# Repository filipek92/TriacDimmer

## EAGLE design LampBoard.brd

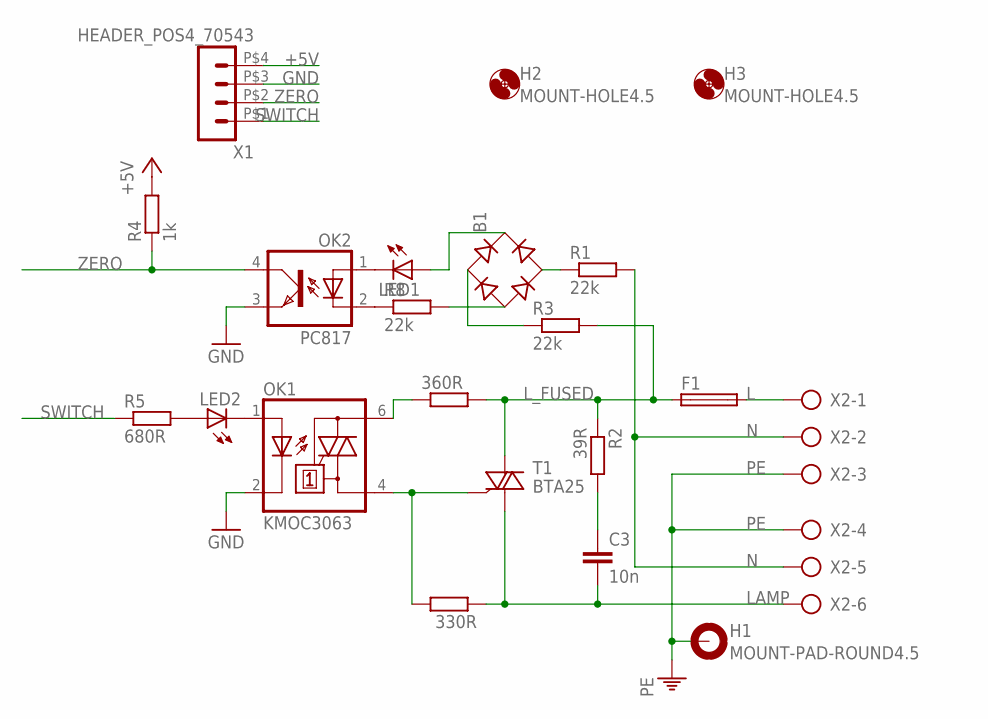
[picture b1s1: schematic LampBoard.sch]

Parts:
330R, 360R: R-EU_0411/12; 0411/12
B1: B-DIL
C3: 10n; C050-045X075
F1: SH22,5A
H1: MOUNT-PAD-ROUND4.5; 4,5-PAD
H2, H3: MOUNT-HOLE4.5; 4,5
LED1, LED2: LED3MM
OK1: KMOC3063; DIL06
OK2: PC817; DIL04
R1, R3, R8: 22k; 0207/10
R2: 39R; 0411/12
R4: 1k; M0805
R5: 680R; M0805
T1: BTA25; TO220BV
X1: HEADER_POS4_70543; 70543-POS4
X2: AK300/6

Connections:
22K: B1.AC2, R1.1
+5V: R4.2, X1.P$4 (4)
GND: OK1.2 (C), OK2.3 (EMIT), X1.P$3 (3)
L: F1.2, X2.1
LAMP: 330R.1, C3.2, T1.T1 (A1), X2.6
L_FUSED: 360R.2, F1.1, R2.1, R3.2, T1.T2 (A2)
N: R1.2, X2.2, X2.5
unnamed: C3.1, R2.2
unnamed: 360R.1, OK1.6 (A2)
unnamed: 330R.2, OK1.4 (A1), T1.G
unnamed: LED1.K (C), OK2.1 (A)
unnamed: B1.AC1, R3.1
unnamed: LED2.K (C), OK1.1 (A)
unnamed: OK2.2 (C), R8.1
unnamed: B1.+, LED1.A
unnamed: LED2.A, R5.2
unnamed: B1.-, R8.2
PE: H1.B4,5, X2.3, X2.4
SWITCH: R5.1, X1.P$1 (1)
ZERO: OK2.4 (COL), R4.1, X1.P$2 (2)

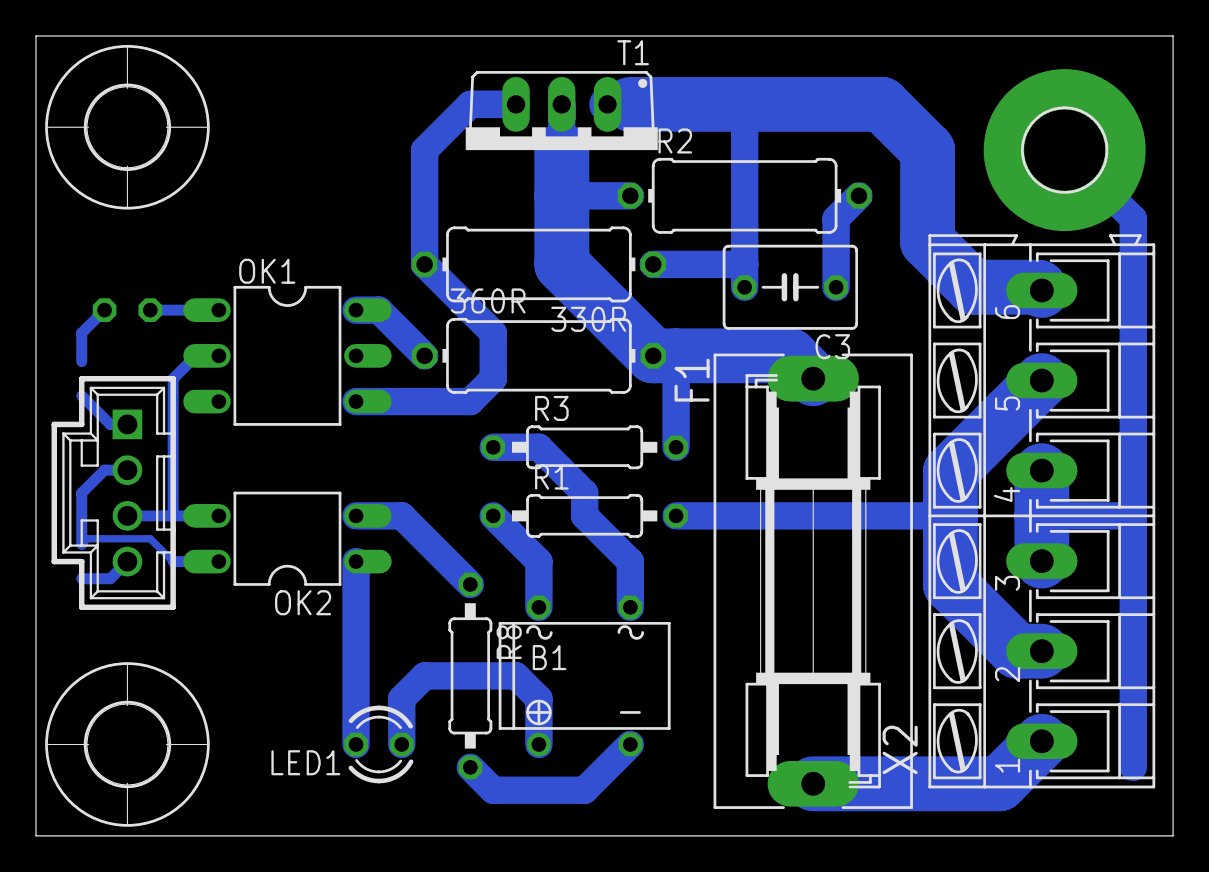
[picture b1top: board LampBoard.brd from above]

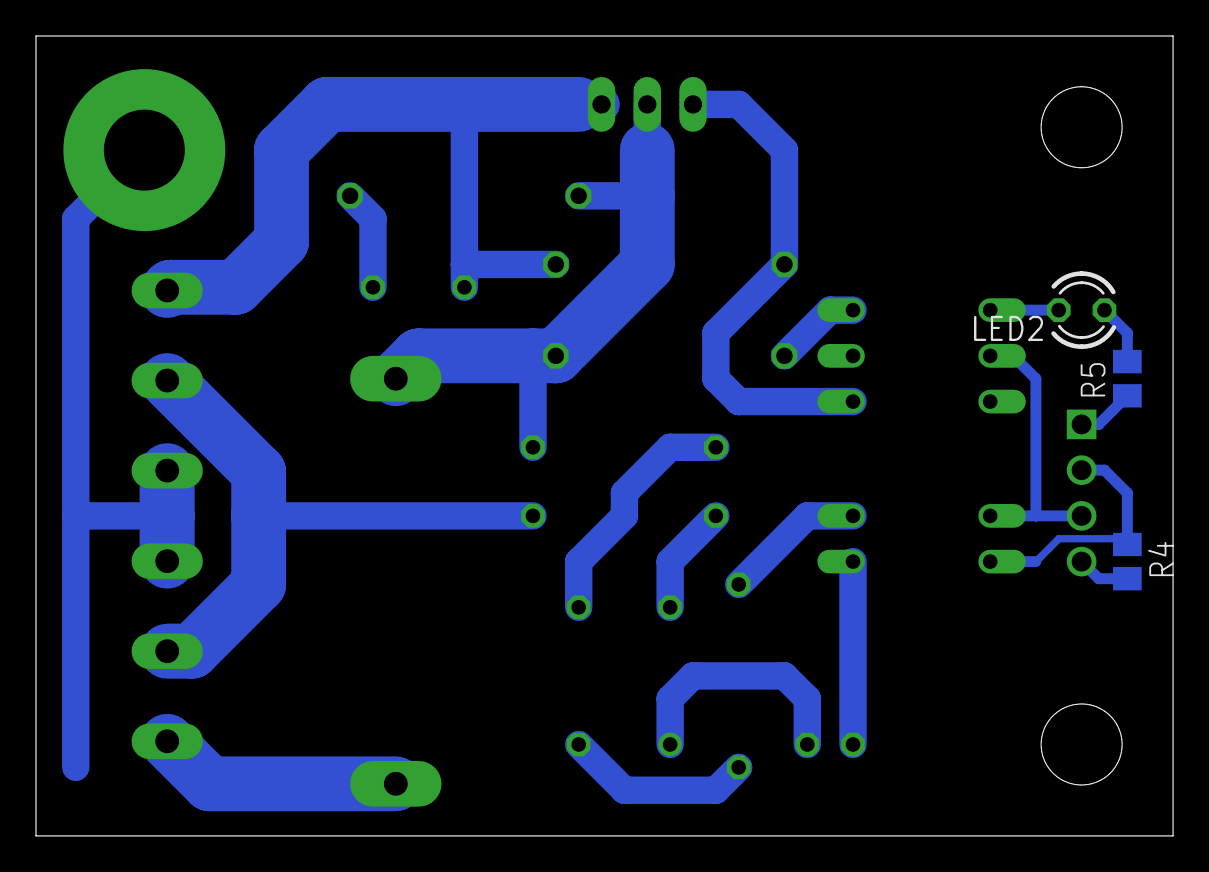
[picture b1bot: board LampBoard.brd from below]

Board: 2 copper layers, 63.2 x 44.4 mm, 21 parts (3 on the bottom side), 20 nets.

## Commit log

2016-07-30 Initialization
2016-07-30 AC section routed
2016-07-30 Routing, refacotring
2016-07-30 Procesor moved away from Power board
